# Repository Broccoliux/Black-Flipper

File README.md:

# FLIPPER BLACK

Flipper black is custom made hacking tool, it can out perfrom flipper Zero in almost every aspect. it have better and larger dsplay and have more power and range then flipper zero.

# Why i built this

I wanted a flipper zero but when i researched about it. i found out that just buying a Flipper Zero is almost useless, to unlock its full power we need to spend more $$, so i decided to build my own with everything in it, no external attachments needed.

# Zine

### CAD n Assembly

### PCB

### Assembly

1. place the PCB in the enclosure.
2. secure the PCB with M2 screws.
3. Connect the display to FPC connector.
4. connect the antenna at top.
5. close with top enclosure and secure with screws.

## Features / components

- 4 layer PCB
- only ICs no modules used.
- Wi-Fi 802.11 built in
- BLE 5.0
- CC1101
- PN532
- MAX-M8Q
- Waveshare 3.5" IPS capacitive touchscreen
- W25Q128
- MicroSD
- TP4056
- TLV70018
- TXB0102
- Firmware based on ESP-IDF
- **Estimated BOM Cost:** $280–$350

## Firmware

**Status:** linked as a submodule

- Firmware is maintained in a differnt repository: https://github.com/fussdeek-del/Black-Flipper-firmware
- The firmware repository is included here as a git submodule at `external/firmware`.

To initialize the submodule locally after cloning:

```bash
git clone https://github.com/fussdeek-del/Black-Flipper
cd Black-Flipper
git checkout integrate/firmware-submodule-fix
git submodule update --init --recursive
```

To build the firmware (see the firmware repo):

```bash
cd external/firmware
idf.py build
```

 ### how to replicate

1. Get the gerber zip form repo and order the PCB from JLCPCB.
2. after receiving the PCB flash the firmware.
3. take the .step files from the repo and order the encloure.
4. here u go, u got custom flipper Black.

## Repository Structure
```

```text
Flipper-Black/
├── PCB/                        # KiCad project + Gerbers
├── CAD/                        # Fusion 360 enclosure (.step)
├── flipper black firmware/     # ESP-IDF firmware + architecture
├── Flipper Black guide pdfs/   # Documentation and guides
├── imgs/                       # Photos and renders
├── BOM/                        # Bill of Materials
└── README.md
```

### built by 

***broccoli 🥦***

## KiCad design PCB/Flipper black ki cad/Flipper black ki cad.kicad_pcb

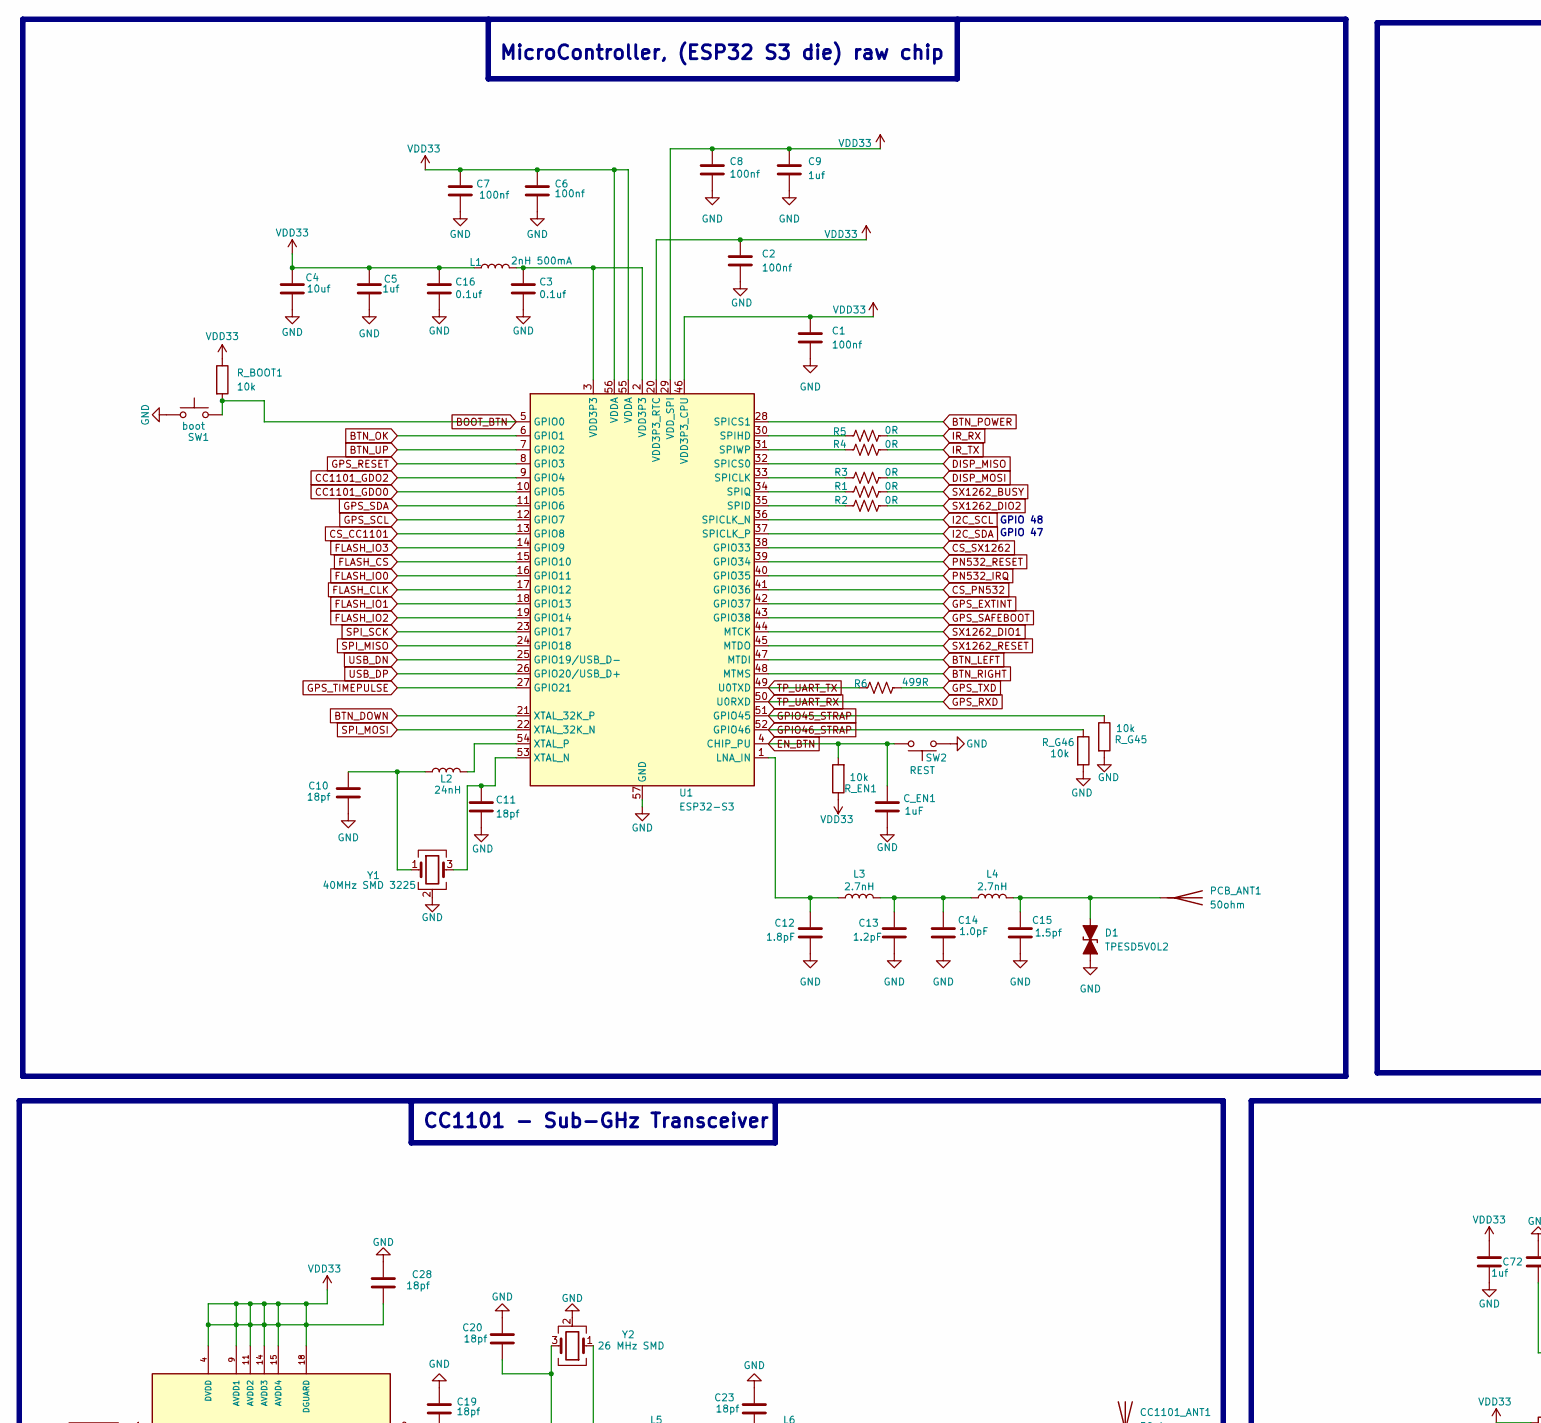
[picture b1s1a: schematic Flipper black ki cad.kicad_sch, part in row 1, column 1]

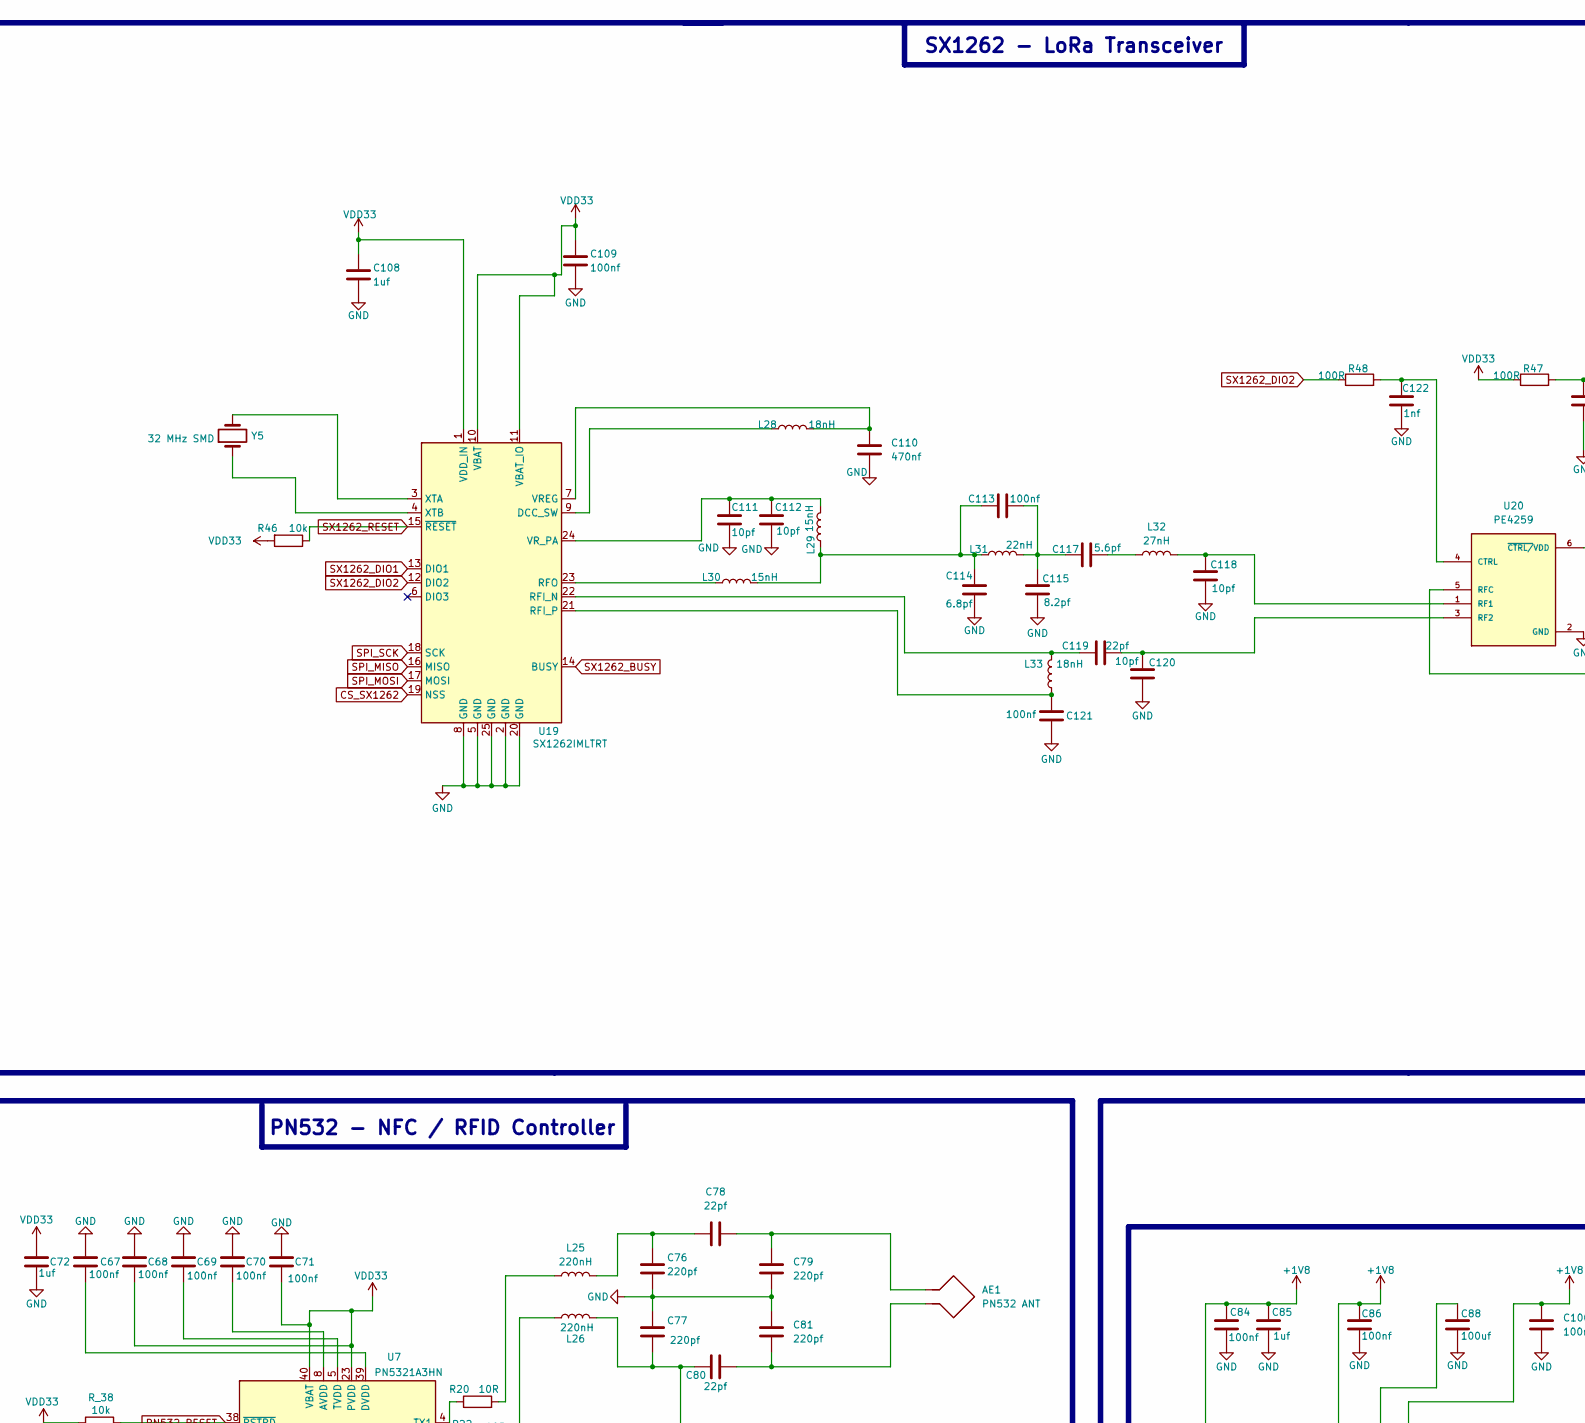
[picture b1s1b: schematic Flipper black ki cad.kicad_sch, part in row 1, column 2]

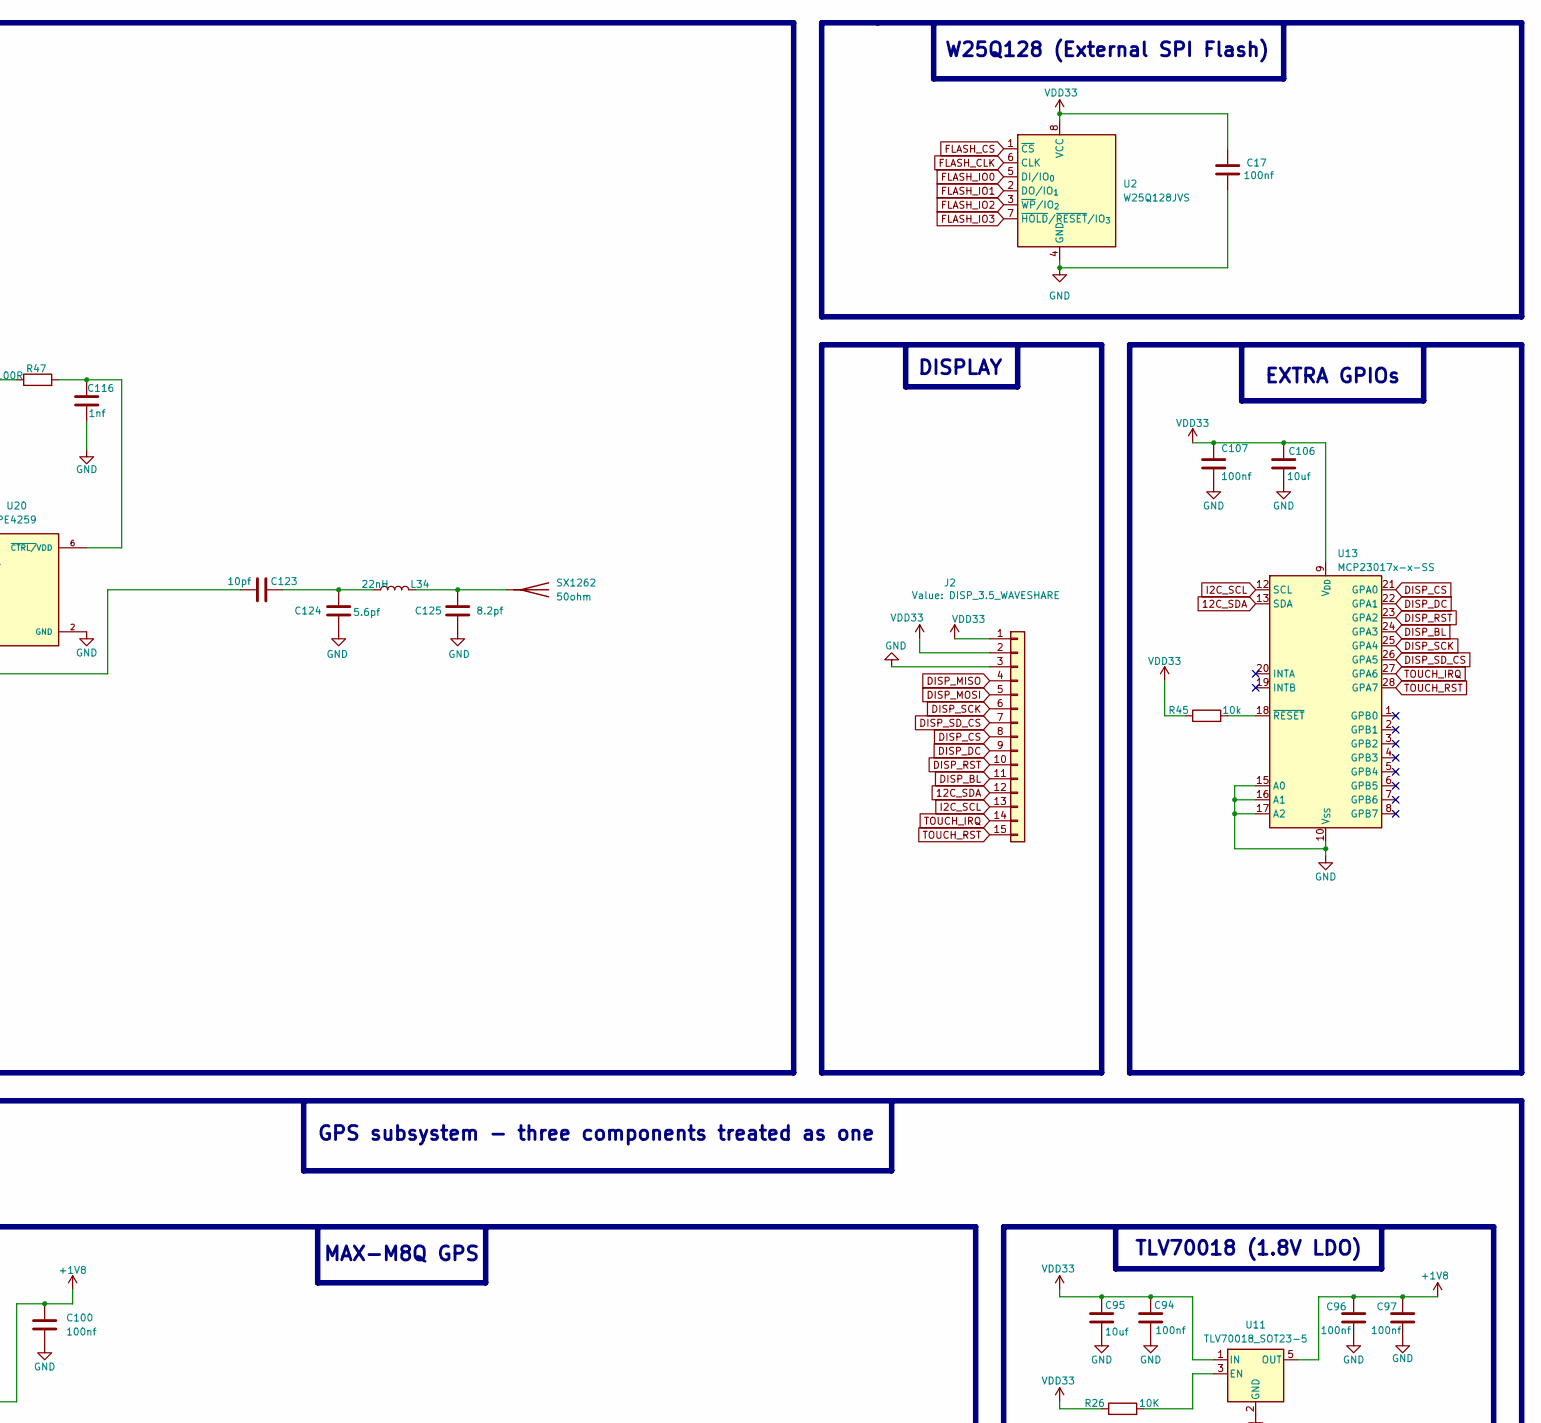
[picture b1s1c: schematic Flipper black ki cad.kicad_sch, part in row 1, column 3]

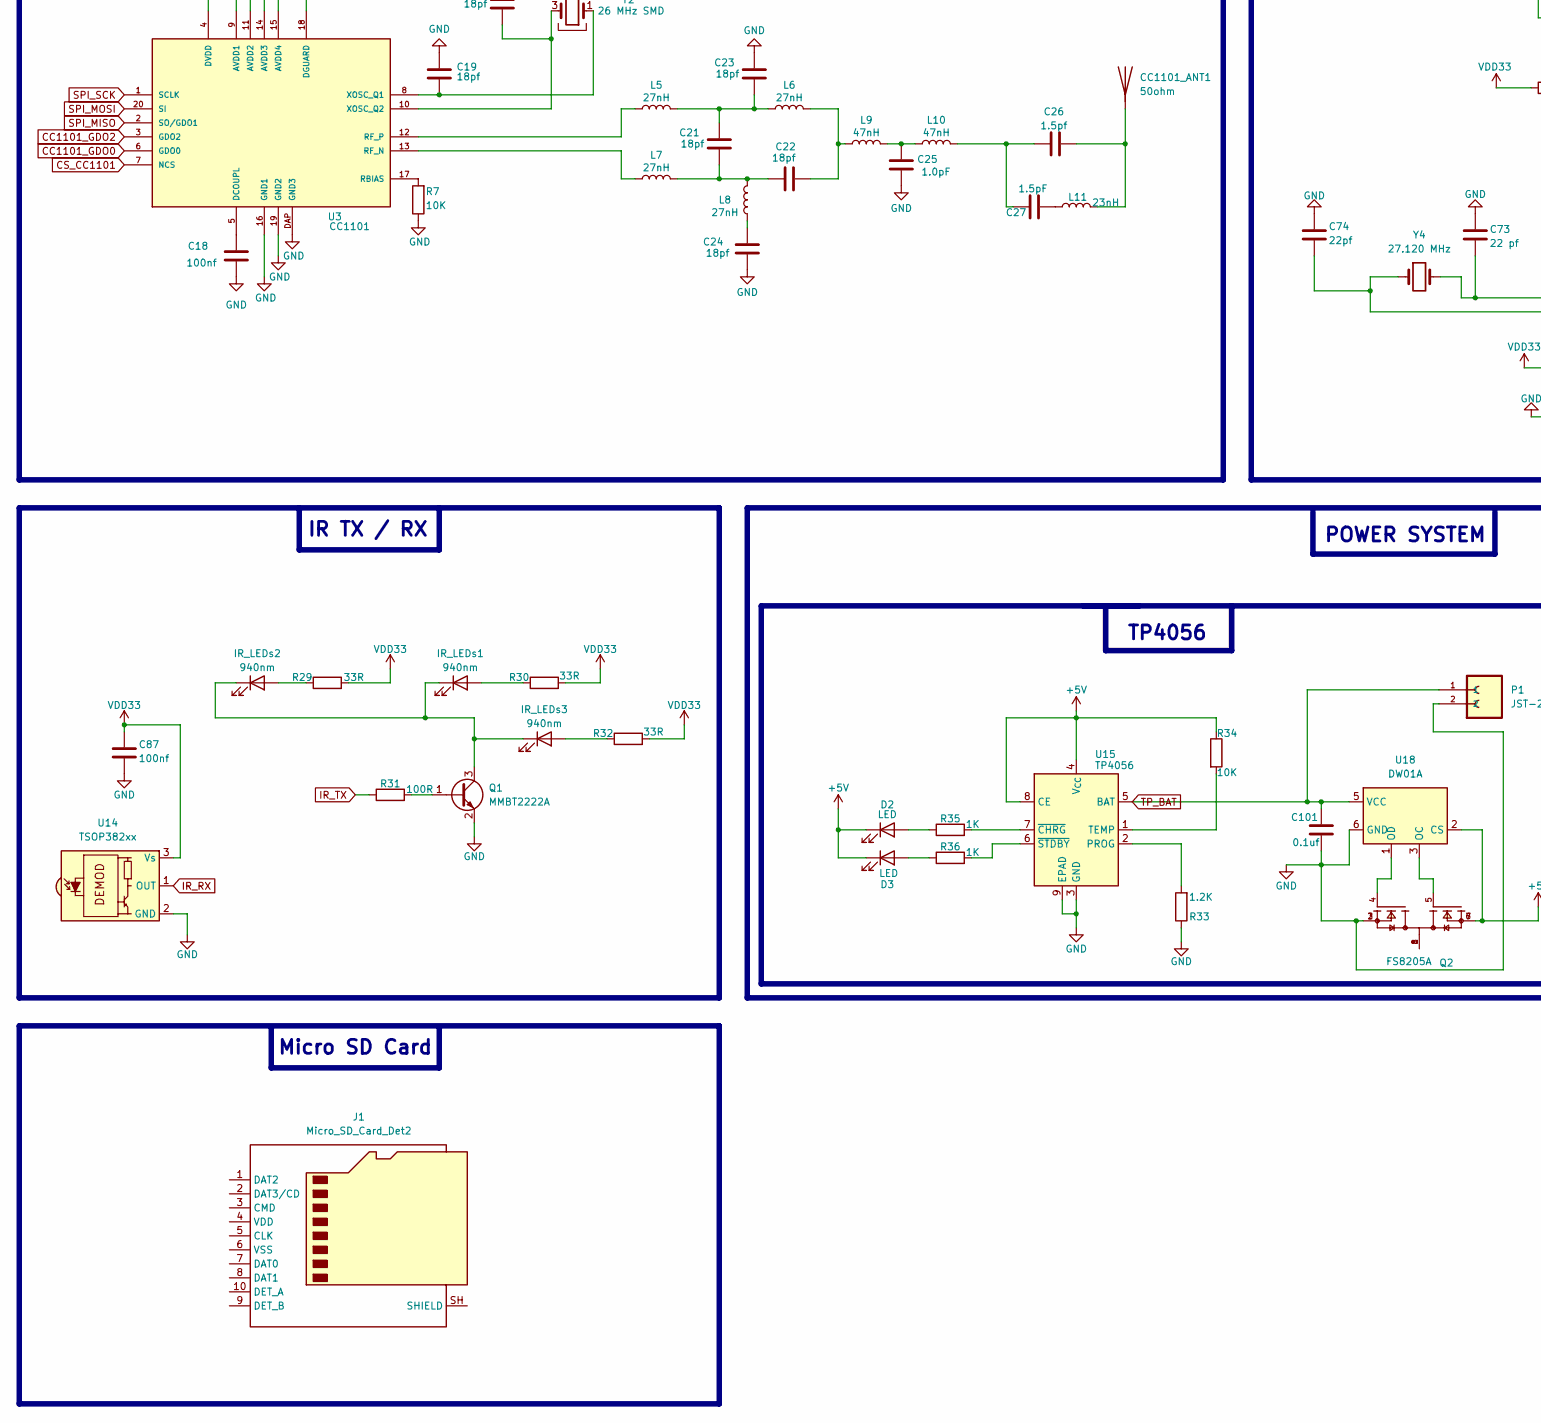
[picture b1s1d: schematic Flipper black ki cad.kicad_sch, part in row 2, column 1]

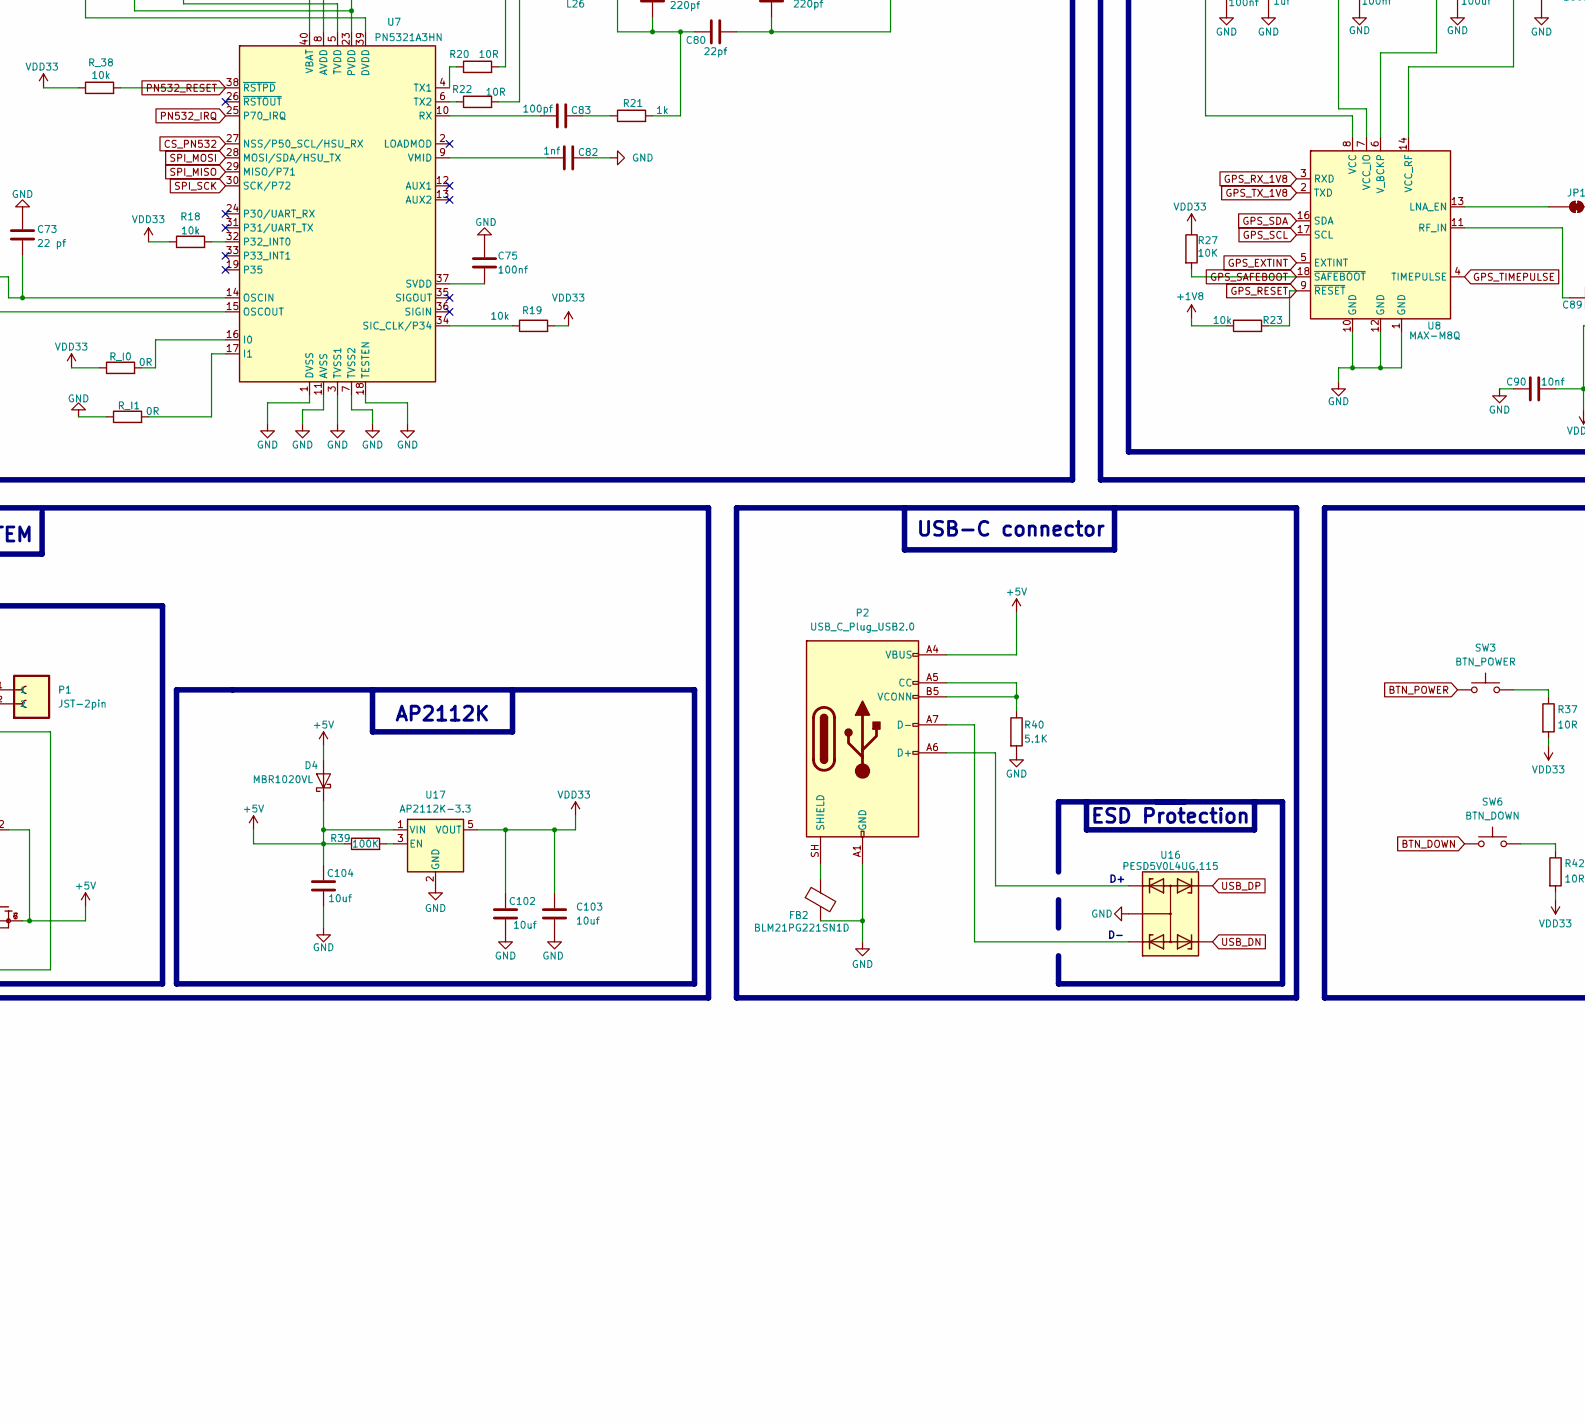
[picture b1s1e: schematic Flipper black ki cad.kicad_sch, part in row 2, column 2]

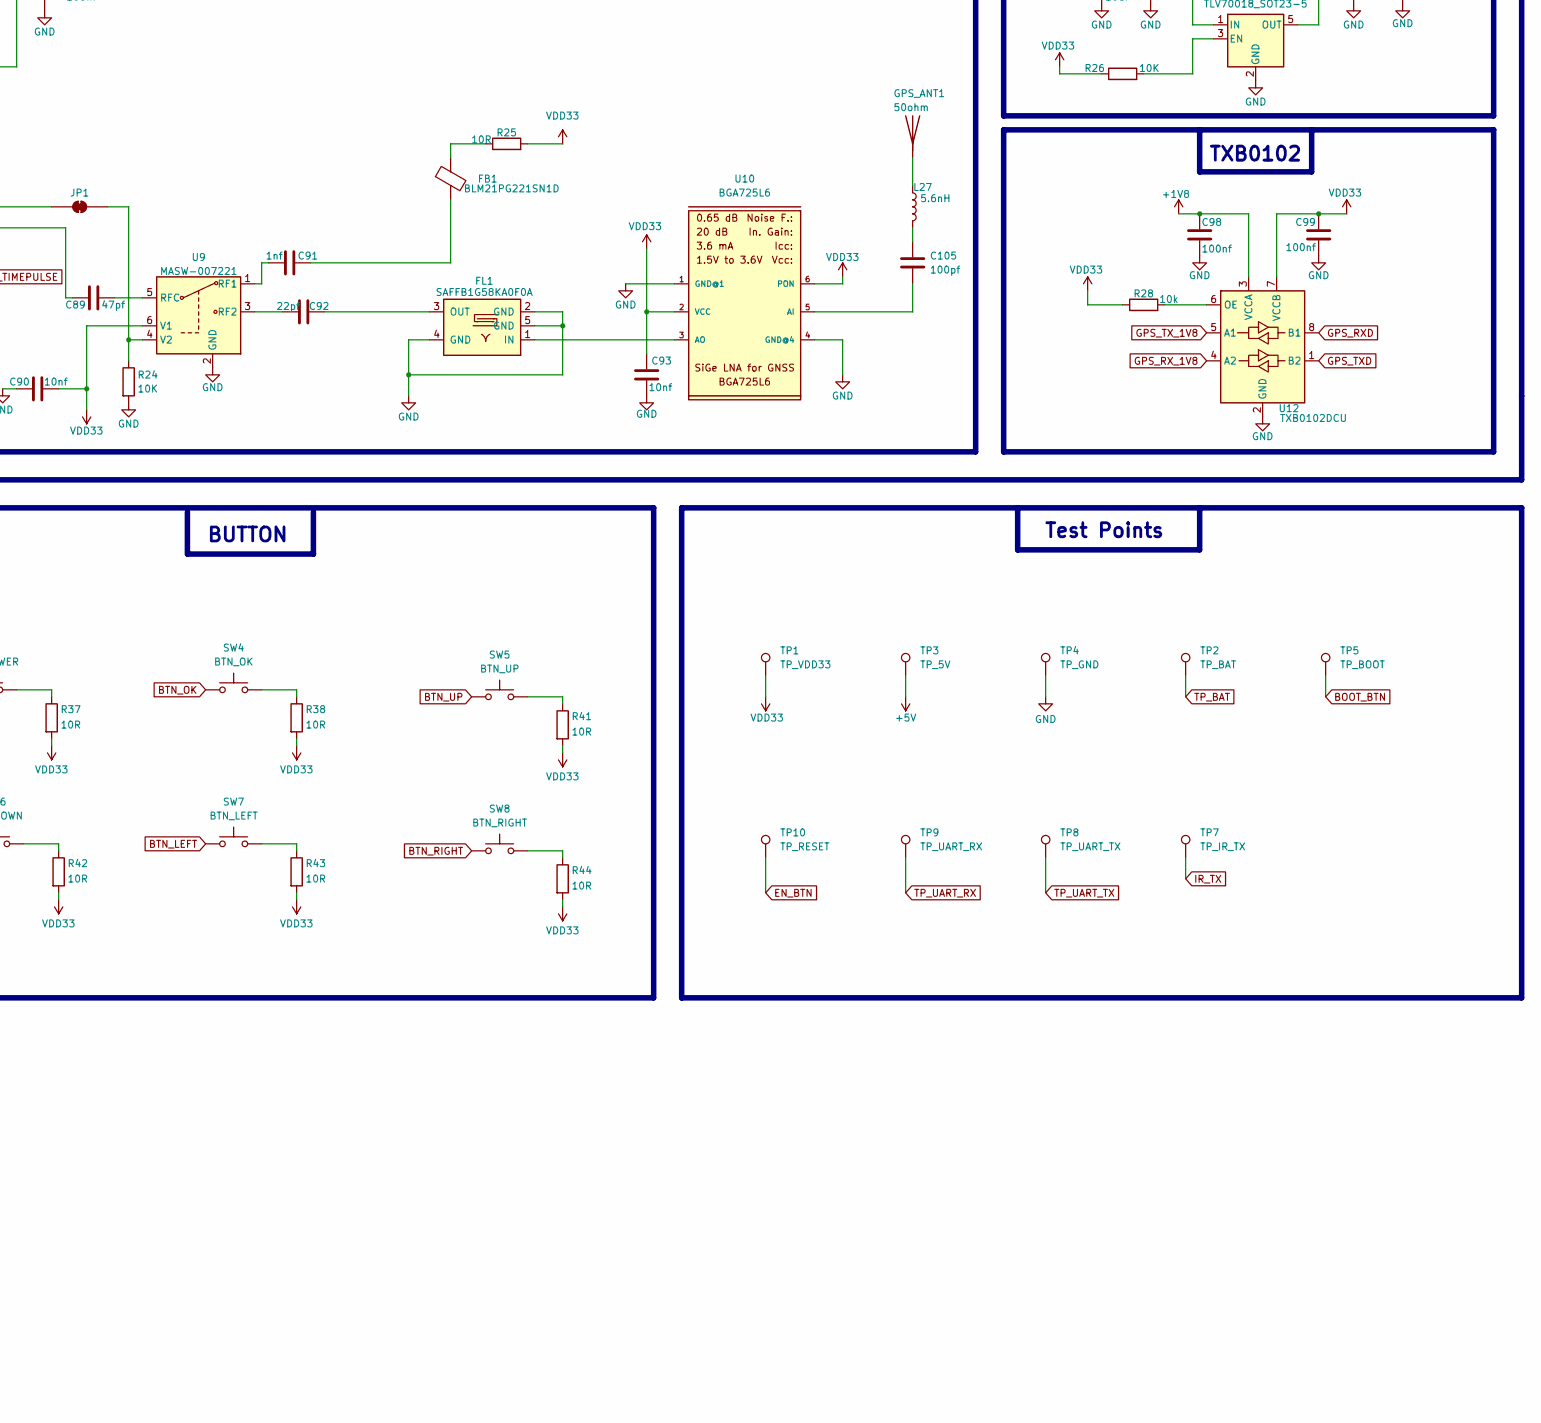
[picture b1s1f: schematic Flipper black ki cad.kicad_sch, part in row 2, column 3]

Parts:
AE1: PN532 ANT; NFC_45x45_N4_NXP_PN5180
C1, C2, C6, C7, C8, C17, C18, C67, C68, C69, C70, C71, C75, C84, C86, C87, C94, C96, C97, C98, C99, C100, C107, C109, C113, C121: 100nf; C_0603_1608Metric_Pad1.08x0.95mm_HandSolder
C3, C16, C101: 0.1uf; C_0603_1608Metric_Pad1.08x0.95mm_HandSolder
C4, C95, C102, C103, C104, C106: 10uf; C_0603_1608Metric_Pad1.08x0.95mm_HandSolder
C5, C9, C72, C85, C108: 1uf; C_0603_1608Metric_Pad1.08x0.95mm_HandSolder
C10, C11, C19, C20, C21, C22, C23, C24, C28: 18pf; C_0603_1608Metric_Pad1.08x0.95mm_HandSolder
C12: 1.8pF; C_0603_1608Metric_Pad1.08x0.95mm_HandSolder
C13: 1.2pF; C_0603_1608Metric_Pad1.08x0.95mm_HandSolder
C14, C25: 1.0pF; C_0603_1608Metric_Pad1.08x0.95mm_HandSolder
C15, C26: 1.5pf; C_0603_1608Metric_Pad1.08x0.95mm_HandSolder
C27: 1.5pF; C_0603_1608Metric_Pad1.08x0.95mm_HandSolder
C73: 22 pf; C_0603_1608Metric_Pad1.08x0.95mm_HandSolder
C74, C78, C80, C92, C119: 22pf; C_0603_1608Metric_Pad1.08x0.95mm_HandSolder
C76, C77, C79, C81: 220pf; C_0603_1608Metric_Pad1.08x0.95mm_HandSolder
C82, C91, C116, C122: 1nf; C_0603_1608Metric_Pad1.08x0.95mm_HandSolder
C83, C105: 100pf; C_0603_1608Metric_Pad1.08x0.95mm_HandSolder
C88: 100uf; C_0603_1608Metric_Pad1.08x0.95mm_HandSolder
C89: 47pf; C_0603_1608Metric_Pad1.08x0.95mm_HandSolder
C90, C93: 10nf; C_0603_1608Metric_Pad1.08x0.95mm_HandSolder
C110: 470nf; C_0603_1608Metric_Pad1.08x0.95mm_HandSolder
C111, C112, C118, C120, C123: 10pf; C_0603_1608Metric_Pad1.08x0.95mm_HandSolder
C114: 6.8pf; C_0603_1608Metric_Pad1.08x0.95mm_HandSolder
C115, C125: 8.2pf; C_0603_1608Metric_Pad1.08x0.95mm_HandSolder
C117, C124: 5.6pf; C_0603_1608Metric_Pad1.08x0.95mm_HandSolder
CC1101_ANT1: 50ohm; U.FL_Hirose_U.FL-R-SMT-1_Vertical
C_EN1: 1uF; C_0603_1608Metric_Pad1.08x0.95mm_HandSolder
D1: TPESD5V0L2; D_SOD-323_HandSoldering
D2, D3: LED; LED_0603_1608Metric_Pad1.05x0.95mm_HandSolder
D4: MBR1020VL; D_SOD-123F
FB1, FB2: BLM21PG221SN1D; L_0603_1608Metric_Pad1.05x0.95mm_HandSolder
FL1: SAFFB1G58KA0F0A; Filter_1109-5_1.1x0.9mm
GPS_ANT1: 50ohm; U.FL_Hirose_U.FL-R-SMT-1_Vertical
IR_LEDs1, IR_LEDs2, IR_LEDs3: 940nm; LED_1206_3216Metric
J1: Micro_SD_Card_Det2
J2: Value: DISP_3.5_WAVESHARE; Amphenol_F32Q-1A7x1-11015_1x15-1MP_P0.5mm_Horizontal
JP1: SolderJumper_2_Bridged; SolderJumper-2_P1.3mm_Bridged2Bar_Pad1.0x1.5mm
L1: 2nH 500mA; L_0603_1608Metric_Pad1.05x0.95mm_HandSolder
L2: 24nH; L_0603_1608Metric_Pad1.05x0.95mm_HandSolder
L3, L4: 2.7nH; L_0603_1608Metric_Pad1.05x0.95mm_HandSolder
L5, L6, L7, L8, L32: 27nH; L_0603_1608Metric_Pad1.05x0.95mm_HandSolder
L9, L10: 47nH; L_0603_1608Metric_Pad1.05x0.95mm_HandSolder
L11: 23nH; L_0603_1608Metric_Pad1.05x0.95mm_HandSolder
L25, L26: 220nH; L_0603_1608Metric_Pad1.05x0.95mm_HandSolder
L27: 5.6nH; L_0603_1608Metric_Pad1.05x0.95mm_HandSolder
L28, L33: 18nH; L_0603_1608Metric_Pad1.05x0.95mm_HandSolder
L29, L30: 15nH; L_0603_1608Metric_Pad1.05x0.95mm_HandSolder
L31, L34: 22nH; L_0603_1608Metric_Pad1.05x0.95mm_HandSolder
P1: JST-2pin; JST_PH_S2B-PH-SM4-TB_1x02-1MP_P2.00mm_Horizontal
P2: USB_C_Plug_USB2.0; USB_C_Receptacle_GCT_USB4105-xx-A_16P_TopMnt_Horizontal
PCB_ANT1: 50ohm; U.FL_Hirose_U.FL-R-SMT-1_Vertical
Q1: MMBT2222A; SOT-23
Q2: FS8205A; SOP65P640X120-8N; PARTREV 1.7
R1, R2, R3, R4, R5: 0R; R_0402_1005Metric
R6: 499R; R_0402_1005Metric
R7, R24, R26, R27, R34: 10K; R_0402_1005Metric
R18, R19, R23, R28, R45, R46: 10k; R_0402_1005Metric
R20, R22, R25, R37, R38, R41, R42, R43, R44: 10R; R_0402_1005Metric
R21: 1k; R_0402_1005Metric
R29, R30, R32: 33R; R_0402_1005Metric
R31, R47, R48: 100R; R_0402_1005Metric
R33: 1.2K; R_0402_1005Metric
R35, R36: 1K; R_0402_1005Metric
R39: 100K; R_0402_1005Metric
R40: 5.1K; R_0402_1005Metric
R_38: 10k; R_0402_1005Metric
R_BOOT1: 10k; R_0402_1005Metric
R_EN1: 10k; R_0402_1005Metric
R_G45, R_G46: 10k; R_0402_1005Metric
R_I0, R_I1: 0R; R_0402_1005Metric
SW1: boot; SW_SPST_B3U-1000P
SW2: REST; SW_SPST_B3U-1000P
SW3: BTN_POWER; SW_PTS645SH43SMTR92LFS
SW4: BTN_OK; SW_PTS645SH43SMTR92LFS
SW5: BTN_UP; SW_PTS645SH43SMTR92LFS
SW6: BTN_DOWN; SW_PTS645SH43SMTR92LFS
SW7: BTN_LEFT; SW_PTS645SH43SMTR92LFS
SW8: BTN_RIGHT; SW_PTS645SH43SMTR92LFS
SX1262: 50ohm; U.FL_Hirose_U.FL-R-SMT-1_Vertical
TP1: TP_VDD33; TestPoint_Pad_D1.0mm
TP2: TP_BAT; TestPoint_Pad_D1.0mm
TP3: TP_5V; TestPoint_Pad_D1.0mm
TP4: TP_GND; TestPoint_Pad_D1.0mm
TP5: TP_BOOT; TestPoint_Pad_D1.0mm
TP7: TP_IR_TX; TestPoint_Pad_D1.0mm
TP8: TP_UART_TX; TestPoint_Pad_D1.0mm
TP9: TP_UART_RX; TestPoint_Pad_D1.0mm
TP10: TP_RESET; TestPoint_Pad_D1.0mm
U1: ESP32-S3; QFN-56-1EP_7x7mm_P0.4mm_EP4x4mm
U2: W25Q128JVS; SOIC-8_5.3x5.3mm_P1.27mm
U3: CC1101; QLP20
U7: PN5321A3HN; HVQFN-40-1EP_6x6mm_P0.5mm_EP4.1x4.1mm
U8: MAX-M8Q; ublox_MAX
U9: MASW-007221; SOT-363_SC-70-6
U10: BGA725L6; BGA725L6E6327
U11: TLV70018_SOT23-5; SOT-23-5
U12: TXB0102DCU; VSSOP-8_2.3x2mm_P0.5mm
U13: MCP23017x-x-SS; SSOP-28_5.3x10.2mm_P0.65mm
U14: TSOP382xx; Vishay_MINICAST-3Pin
U15: TP4056; SOIC-8-1EP_3.9x4.9mm_P1.27mm_EP2.41x3.3mm_ThermalVias
U16: PESD5V0L4UG,115; SOT65P210X110-5N; PARTREV 04
U17: AP2112K-3.3; SOT-23-5
U18: DW01A; SOT-23-6
U19: SX1262IMLTRT; QFN50P400X400X100-25N
U20: PE4259; SOT65P215X110-6N
Y1: 40MHz SMD 3225; Crystal_SMD_2016-4Pin_2.0x1.6mm
Y2: 26 MHz SMD; Crystal_SMD_2016-4Pin_2.0x1.6mm
Y4: 27.120 MHz; Crystal_SMD_2016-4Pin_2.0x1.6mm
Y5: 32 MHz SMD; Crystal_SMD_2016-4Pin_2.0x1.6mm

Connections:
12C_SDA: J2.12, U13.13 (SDA)
+1V8: C84.1, C85.1, C86.1, C96.1, C97.1, C98.1, C100.1, R23.1, U8.7 (VCC_IO), U8.8 (VCC), U8.14 (VCC_RF), U11.5 (OUT), U12.3 (VCCA)
+5V: C104.1, D2.1 (K), D3.1 (K), D4.1 (K), D4.2 (A), P2.A4 (VBUS), P2.A9 (VBUS), P2.B4 (VBUS), P2.B9 (VBUS), Q2.6, Q2.7, R34.1, R39.1, TP3.1 (1_1), U15.4 (V_{CC}), U15.8 (CE), U17.1 (VIN), U18.2 (CS)
BOOT_BTN: R_BOOT1.2, SW1.2, TP5.1 (1_1), U1.5 (GPIO0)
BTN_DOWN: SW6.1, U1.21 (XTAL_32K_P)
BTN_LEFT: SW7.1, U1.47 (MTDI)
BTN_OK: SW4.1, U1.6 (GPIO1)
BTN_POWER: SW3.1, U1.28 (SPICS1)
BTN_RIGHT: SW8.1, U1.48 (MTMS)
BTN_UP: SW5.1, U1.7 (GPIO2)
CC1101_GDO0: U1.10 (GPIO5), U3.6 (GDO0)
CC1101_GDO2: U1.9 (GPIO4), U3.3 (GDO2)
CS_CC1101: U1.13 (GPIO8), U3.7 (NCS)
CS_PN532: U1.41 (GPIO36), U7.27 (NSS/P50_SCL/HSU_RX)
CS_SX1262: U1.38 (GPIO33), U19.19 (NSS)
DISP_BL: J2.11, U13.24 (GPA3)
DISP_CS: J2.8, U13.21 (GPA0)
DISP_DC: J2.9, U13.22 (GPA1)
DISP_MISO: J2.4, U1.32 (SPICS0)
DISP_MOSI: J2.5, R3.2
DISP_RST: J2.10, U13.23 (GPA2)
DISP_SCK: J2.6, U13.25 (GPA4)
DISP_SD_CS: J2.7, U13.26 (GPA5)
EN_BTN: C_EN1.1, R_EN1.2, SW2.2, TP10.1 (1_1), U1.4 (CHIP_PU)
FLASH_CLK: U1.17 (GPIO12), U2.6 (CLK)
FLASH_CS: U1.15 (GPIO10), U2.1 (~CS)
FLASH_IO0: U1.16 (GPIO11), U2.5 (DI/IO_{0})
FLASH_IO1: U1.18 (GPIO13), U2.2 (DO/IO_{1})
FLASH_IO2: U1.19 (GPIO14), U2.3 (~WP/IO_{2})
FLASH_IO3: U1.14 (GPIO9), U2.7 (~HOLD/~RESET/IO_{3})
GND: C1.2, C2.2, C3.2, C4.2, C5.2, C6.2, C7.2, C8.2, C9.2, C10.2, C11.2, C12.2, C13.2, C14.2, C15.2, C16.2, C17.2, C18.2, C19.1, C20.1, C23.1, C24.2, C25.2, C28.1, C67.1, C68.1, C69.1, C70.1, C71.1, C72.2, C73.1, C74.1, C75.1, C76.2, C77.1, C79.1, C81.2, C82.2, C84.2, C85.2, C86.2, C87.2, C88.2, C90.1, C93.2, C94.2, C95.2, C96.2, C97.2, C98.2, C99.2, C100.2, C101.2, C102.2, C103.2, C104.2, C106.2, C107.2, C108.2, C109.2, C110.2, C111.2, C112.2, C114.2, C115.2, C116.2, C118.2, C120.1, C121.1, C122.2, C124.1, C125.1, C_EN1.2, D1.2 (A2), FB2.2, FL1.2 (GND), FL1.4 (GND), FL1.5 (GND), J2.3, P1.2, P2.A1 (GND), P2.A12 (GND), P2.B1 (GND), P2.B12 (GND), Q1.2 (E), Q2.2, Q2.3, R7.1, R24.2, R33.1, R40.2, R_G45.2, R_G46.2, R_I1.1, SW1.1, SW2.1, TP4.1 (1_1), U1.57 (GND), U2.4 (GND), U3.16 (GND1), U3.19 (GND2), U3.DAP (GND3), U7.1 (DVSS), U7.3 (TVSS1), U7.7 (TVSS2), U7.11 (AVSS), U7.18 (TESTEN), U7.41 (AVSS), U8.1 (GND), U8.10 (GND), U8.12 (GND), U9.2 (GND), U10.1 (GND@1), U10.4 (GND@4), U11.2 (GND), U12.2 (GND), U13.10 (V_{SS}), U13.15 (A0), U13.16 (A1), U13.17 (A2), U14.2 (GND), U15.3 (GND), U15.9 (EPAD), U16.2, U17.2 (GND), U18.6 (GND), U19.2 (GND), U19.5 (GND), U19.8 (GND), U19.20 (GND), U19.25 (GND), U20.2 (GND), Y1.2 (GND), Y2.2 (GND)
GPIO45_STRAP: R_G45.1, U1.51 (GPIO45)
GPIO46_STRAP: R_G46.1, U1.52 (GPIO46)
GPS_EXTINT: U1.42 (GPIO37), U8.5 (EXTINT)
GPS_RESET: R23.2, U1.8 (GPIO3), U8.9 (~RESET)
GPS_RXD: TP9.1 (1_1), U1.50 (U0RXD), U12.8 (B1)
GPS_RX_1V8: U8.3 (RXD), U12.4 (A2)
GPS_SAFEBOOT: R27.2, U1.43 (GPIO38), U8.18 (~SAFEBOOT)
GPS_SCL: U1.12 (GPIO7), U8.17 (SCL)
GPS_SDA: U1.11 (GPIO6), U8.16 (SDA)
GPS_TIMEPULSE: U1.27 (GPIO21), U8.4 (TIMEPULSE)
GPS_TXD: R6.2, U12.1 (B2)
GPS_TX_1V8: U8.2 (TXD), U12.5 (A1)
I2C_SCL: J2.13, U1.36 (SPICLK_N), U13.12 (SCL)
I2C_SDA: U1.37 (SPICLK_P)
IR_RX: R5.2, U14.1 (OUT)
IR_TX: R4.2, R31.1, TP7.1 (1_1)
unnamed: AE1.1, C78.2, C79.2
unnamed: AE1.2, C80.2, C81.1
unnamed: C3.1, L1.2, U1.2 (VDD3P3), U1.3 (VDD3P3)
unnamed: C13.1, C14.1, L3.2, L4.1
unnamed: C21.1, C23.2, L5.2, L6.1
unnamed: C21.2, C22.1, L7.2, L8.2
unnamed: C22.2, L6.2, L9.1
unnamed: C24.1, L8.1
unnamed: C25.1, L9.2, L10.1
unnamed: C26.1, C27.1, L10.2
unnamed: C27.2, L11.1
unnamed: C76.1, C78.1, L25.2
unnamed: C77.2, C80.1, L26.2, R21.2
unnamed: C83.2, R21.1
unnamed: C91.2, FB1.2
unnamed: C105.1, L27.2
unnamed: C113.1, C114.1, L29.1, L30.2, L31.1
unnamed: C113.2, C115.1, C117.1, L31.2
unnamed: C117.2, L32.1
unnamed: C123.2, C124.2, L34.1
unnamed: C26.2, CC1101_ANT1.1 (A_1), L11.2
unnamed: C15.1, D1.1 (A1), L4.2, PCB_ANT1.1 (A_1)
unnamed: D2.2 (A), R35.1
unnamed: D3.2 (A), R36.1
unnamed: FB1.1, R25.1
unnamed: FL1.1 (IN), U10.3 (AO)
unnamed: C92.2, FL1.3 (OUT)
unnamed: GPS_ANT1.1 (A_1), L27.1
unnamed: IR_LEDs1.2 (A), R30.1
unnamed: IR_LEDs1.1 (K), IR_LEDs2.1 (K), IR_LEDs3.1 (K), Q1.3 (C)
unnamed: IR_LEDs2.2 (A), R29.1
unnamed: IR_LEDs3.2 (A), R32.1
unnamed: JP1.1 (A), U8.13 (LNA_EN)
unnamed: JP1.2 (B), R24.1, U9.4 (V2)
unnamed: L25.1, R20.2
unnamed: L26.1, R22.2
unnamed: P2.A5 (CC), P2.B5 (VCONN), R40.1
unnamed: P2.A6 (D+), U16.1
unnamed: P2.A7 (D-), U16.3
unnamed: FB2.1, P2.SH (SHIELD)
unnamed: Q1.1 (B), R31.2
unnamed: Q2.1, Q2.8
unnamed: R37.1, SW3.2
unnamed: R38.1, SW4.2
unnamed: R41.1, SW5.2
unnamed: R42.1, SW6.2
unnamed: R43.1, SW7.2
unnamed: R44.1, SW8.2
unnamed: C125.2, L34.2, SX1262.1 (A_1)
unnamed: C12.1, L3.1, U1.1 (LNA_IN)
unnamed: R3.1, U1.33 (SPICLK)
unnamed: R2.1, U1.35 (SPID)
unnamed: R5.1, U1.30 (SPIHD)
unnamed: R1.1, U1.34 (SPIQ)
unnamed: R4.1, U1.31 (SPIWP)
unnamed: C11.1, U1.53 (XTAL_N), Y1.3 (XOUT)
unnamed: L2.2, U1.54 (XTAL_P)
unnamed: C18.1, U3.5 (DCOUPL)
unnamed: R7.2, U3.17 (RBIAS)
unnamed: L7.1, U3.13 (RF_N)
unnamed: L5.1, U3.12 (RF_P)
unnamed: C19.2, U3.8 (XOSC_Q1), Y2.1 (XIN)
unnamed: C20.2, U3.10 (XOSC_Q2), Y2.3 (XOUT)
unnamed: C70.2, U7.8 (AVDD)
unnamed: C67.2, U7.39 (DVDD)
unnamed: R_I0.2, U7.16 (I0)
unnamed: R_I1.2, U7.17 (I1)
unnamed: C73.2, U7.14 (OSCIN), Y4.2
unnamed: C74.2, U7.15 (OSCOUT), Y4.1
unnamed: R18.2, U7.32 (P32_INT0)
unnamed: C83.1, U7.10 (RX)
unnamed: R19.1, U7.34 (SIC_CLK/P34)
unnamed: C75.2, U7.37 (SVDD)
unnamed: C69.2, U7.5 (TVDD)
unnamed: R20.1, U7.4 (TX1)
unnamed: R22.1, U7.6 (TX2)
unnamed: C82.1, U7.9 (VMID)
unnamed: C89.1, U8.11 (RF_IN)
unnamed: C88.1, U8.6 (V_BCKP)
unnamed: C91.1, U9.1 (RF1)
unnamed: C92.1, U9.3 (RF2)
unnamed: C89.2, U9.5 (RFC)
unnamed: C105.2, U10.5 (AI)
unnamed: R26.2, U11.3 (EN)
unnamed: R28.2, U12.6 (OE)
unnamed: R45.2, U13.18 (~RESET)
unnamed: R33.2, U15.2 (PROG)
unnamed: R34.2, U15.1 (TEMP)
unnamed: R35.2, U15.7 (~CHRG)
unnamed: R36.2, U15.6 (~STDBY)
unnamed: R39.2, U17.3 (EN)
unnamed: Q2.5, U18.3 (OC)
unnamed: Q2.4, U18.1 (OD)
unnamed: L28.1, U19.9 (DCC_SW)
unnamed: C119.1, L33.2, U19.22 (RFI_N)
unnamed: C121.2, L33.1, U19.21 (RFI_P)
unnamed: L30.1, U19.23 (RFO)
unnamed: C110.1, L28.2, U19.7 (VREG)
unnamed: C111.1, C112.1, L29.2, U19.24 (VR_PA)
unnamed: U19.3 (XTA), Y5.2
unnamed: U19.4 (XTB), Y5.1
unnamed: C122.1, R48.2, U20.4 (CTRL)
unnamed: C118.1, L32.2, U20.1 (RF1)
unnamed: C119.2, C120.2, U20.3 (RF2)
unnamed: C123.1, U20.5 (RFC)
unnamed: C116.1, R47.2, U20.6 (~CTRL/VDD)
unnamed: C10.1, L2.1, Y1.1 (XIN)
PN532_IRQ: U1.40 (GPIO35), U7.25 (P70_IRQ)
PN532_RESET: R_38.2, U1.39 (GPIO34), U7.38 (~RSTPD)
SPI_MISO: U1.24 (GPIO18), U3.2 (SO/GDO1), U7.29 (MISO/P71), U19.16 (MISO)
SPI_MOSI: U1.22 (XTAL_32K_N), U3.20 (SI), U7.28 (MOSI/SDA/HSU_TX), U19.17 (MOSI)
SPI_SCK: U1.23 (GPIO17), U3.1 (SCLK), U7.30 (SCK/P72), U19.18 (SCK)
SX1262_BUSY: R1.2, U19.14 (BUSY)
SX1262_DIO1: U1.44 (MTCK), U19.13 (DIO1)
SX1262_DIO2: R2.2, R48.1, U19.12 (DIO2)
SX1262_RESET: R46.1, U1.45 (MTDO), U19.15 (~RESET)
TOUCH_IRQ: J2.14, U13.27 (GPA6)
TOUCH_RST: J2.15, U13.28 (GPA7)
TP_BAT: C101.1, P1.1, TP2.1 (1_1), U15.5 (BAT), U18.5 (VCC)
TP_UART_TX: R6.1, TP8.1 (1_1), U1.49 (U0TXD)
USB_DN: U1.25 (GPIO19/USB_D-), U16.4
USB_DP: U1.26 (GPIO20/USB_D+), U16.5
VDD33: C1.1, C2.1, C4.1, C5.1, C6.1, C7.1, C8.1, C9.1, C16.1, C17.1, C28.2, C68.2, C71.2, C72.1, C87.1, C90.2, C93.1, C94.1, C95.1, C99.1, C102.1, C103.1, C106.1, C107.1, C108.1, C109.1, J2.1, J2.2, L1.1, R18.1, R19.2, R25.2, R26.1, R27.1, R28.1, R29.2, R30.2, R32.2, R37.2, R38.2, R41.2, R42.2, R43.2, R44.2, R45.1, R46.2, R47.1, R_38.1, R_BOOT1.1, R_EN1.1, R_I0.1, TP1.1 (1_1), U1.20 (VDD3P3_RTC), U1.29 (VDD_SPI), U1.46 (VDD3P3_CPU), U1.55 (VDDA), U1.56 (VDDA), U2.8 (VCC), U3.4 (DVDD), U3.9 (AVDD1), U3.11 (AVDD2), U3.14 (AVDD3), U3.15 (AVDD4), U3.18 (DGUARD), U7.23 (PVDD), U7.40 (VBAT), U9.6 (V1), U10.2 (VCC), U10.6 (PON), U11.1 (IN), U12.7 (VCCB), U13.9 (V_{DD}), U14.3 (Vs), U17.5 (VOUT), U19.1 (VDD_IN), U19.10 (VBAT), U19.11 (VBAT_IO)

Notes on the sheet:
ESD Protection
MicroController, (ESP32 S3 die) raw chip
TLV70018 (1.8V LDO)
TP4056
GPS subsystem - three components treated as one
GPIO 47
GPIO 48
DISPLAY
USB-C connector
Micro SD Card
CC1101 - Sub-GHz Transceiver
TXB0102
PN532 - NFC / RFID Controller
EXTRA GPIOs
SX1262 - LoRa Transceiver
POWER SYSTEM
MAX-M8Q GPS
AP2112K
W25Q128 (External SPI Flash)
BUTTON
IR TX / RX
Test Points

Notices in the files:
README.md:
License: MIT
